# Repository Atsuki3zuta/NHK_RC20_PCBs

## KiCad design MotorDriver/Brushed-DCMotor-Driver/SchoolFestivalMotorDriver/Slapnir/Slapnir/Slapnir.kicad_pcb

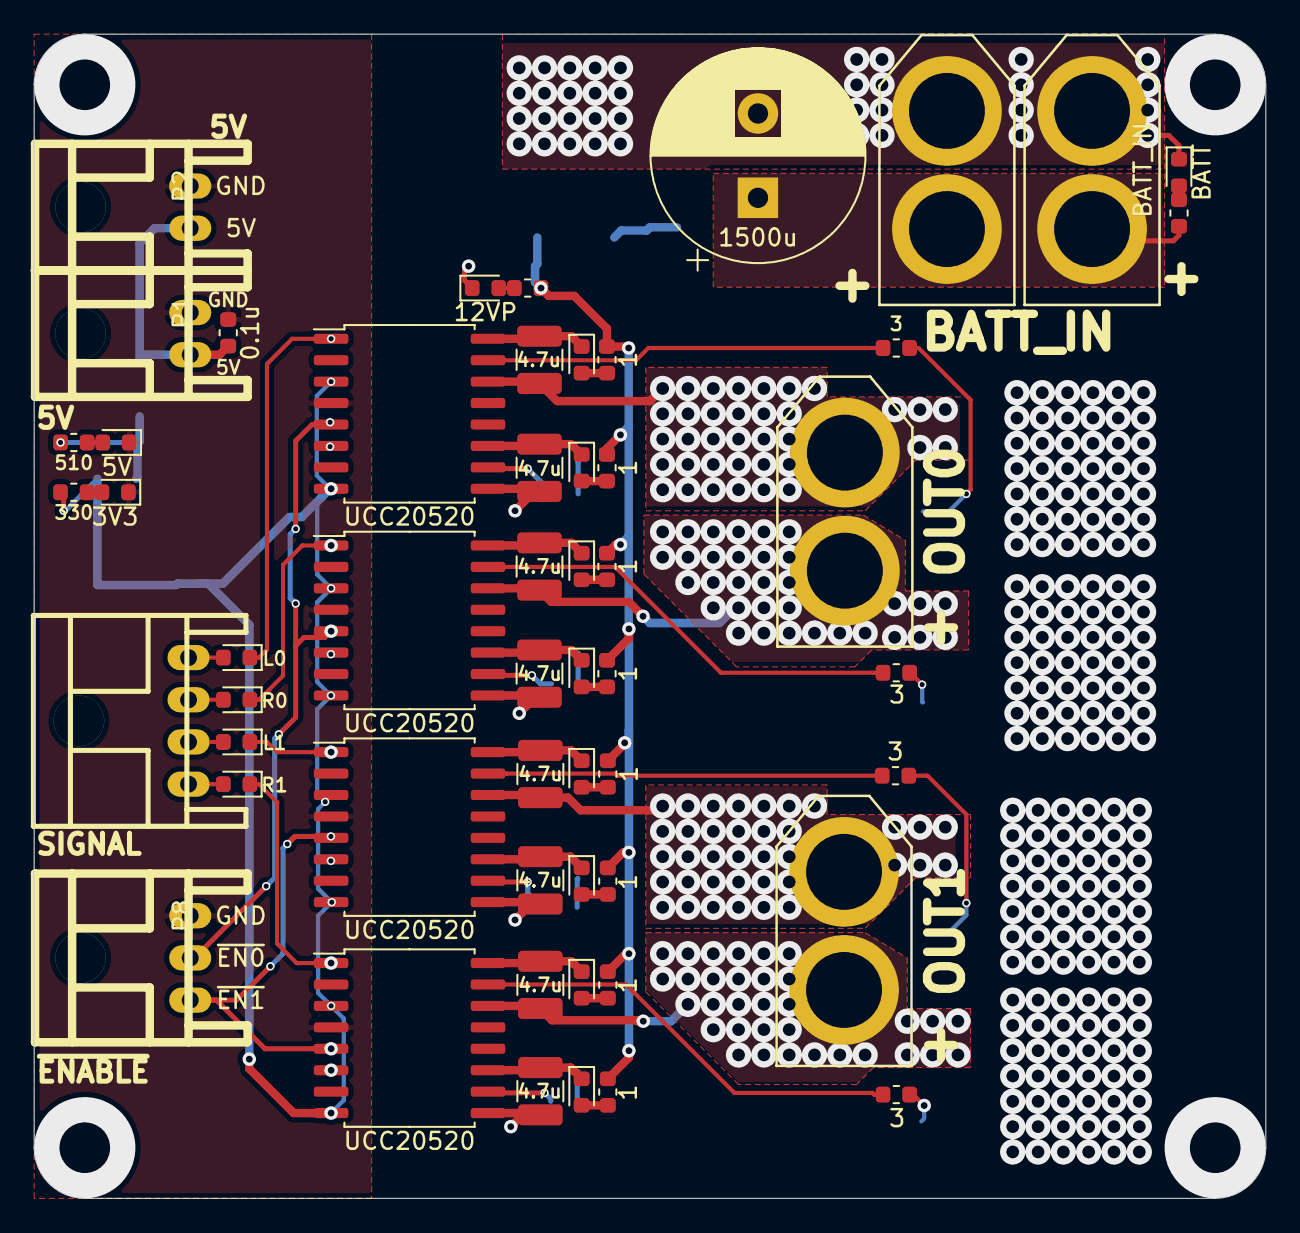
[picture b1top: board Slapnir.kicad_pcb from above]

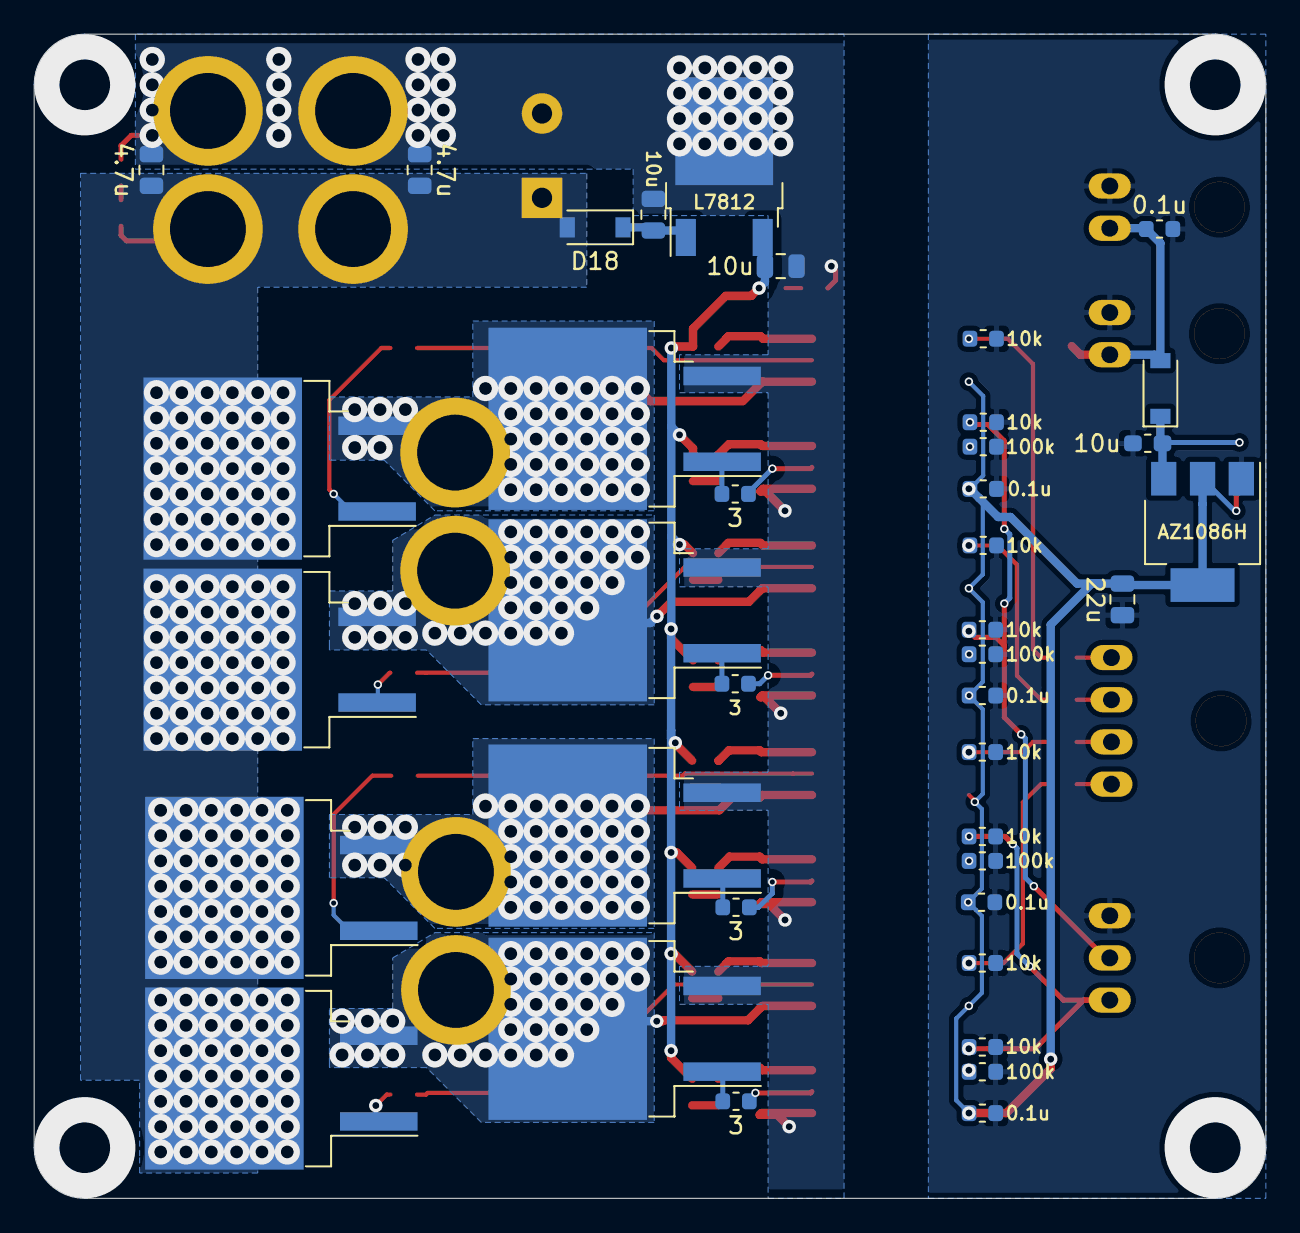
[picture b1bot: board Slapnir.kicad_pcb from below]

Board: 2 copper layers, 73.0 x 69.0 mm, 93 parts (39 on the bottom side), 62 nets.

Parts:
C1: 10u; C_0603_1608Metric_Pad1.05x0.95mm_HandSolder
C2, C3, C5, C6, C7, C8: 0.1u; C_0603_1608Metric
C4: 22u; C_0805_2012Metric
C9, C10, C11, C12, C13, C14, C15, C16: 4.7u; C_1210_3225Metric
C17: 1500u; CP_Radial_D12.5mm_P5.00mm
C18, C20: 4.7u; C_0805_2012Metric
C19, C21: 10u; C_0805_2012Metric
D1, D18: DIODE; D_SOD-123
D2, D3, D4, D5, D8, D9, D10, D11, D12, D13, D14, D15: DIODESCH; D_0603_1608Metric
D6: 5V; LED_0603_1608Metric
D7: 3V3; LED_0603_1608Metric
D16: BATT; LED_0603_1608Metric
D17: 12VP; LED_0603_1608Metric
P1, P2: 5V; XA_2LC
P3: SIGNAL; XA_4LC
P4: BATT_IN; XT60_F
P5: BATT_IN; XT60_M
P6: OUT0; XT60_F
P7: OUT1; XT60_F
P8: ~ENABLE; XA_3LC
Q1, Q2, Q3, Q4, Q5, Q6, Q7, Q8: Q_NMOS_GDS; TO-263-2
R1: 510; R_0603_1608Metric
R2: 330; R_0603_1608Metric
R3, R4, R5, R6, R29, R30, R31, R32: 10k; R_0603_1608Metric
R7, R8, R9, R10: 100k; R_0603_1608Metric
R11, R12, R13, R14, R15, R16, R17, R18: 3; R_0603_1608Metric
R19, R20, R21, R22, R23, R24, R25, R26: 1; R_0603_1608Metric
R27: 2.2k; R_0603_1608Metric
R28: 1.2k; R_0603_1608Metric
U1: AZ1086H; SOT-223-3_TabPin2
U2, U3, U4, U5: UCC20520; SOIC-16W_7.5x10.3mm_P1.27mm
U6: L7812; TO-252-2

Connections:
+3V3: C4.1, C5.1, C6.1, C7.1, C8.1, R2.2, U1.2, U2.3, U2.8, U3.3, U3.8, U4.3, U4.8, U5.3, U5.8
+5V: C1.1, D1.1, R1.2, U1.3
+12P: C21.1, R19.1, R20.1, R21.1, R22.1, R23.1, R24.1, R25.1, R26.1, R28.2, U6.3
+BATT: C17.1, C18.2, C20.2, D18.2, P4.2, P5.2, Q1.2, Q3.2, Q5.2, Q7.2, R27.2
/5V: C2.2, C3.2, D1.2, P1.2, P2.2
/MOTOR0_OUT_L: C9.2, P6.1, Q1.3, Q2.2, U2.14
/MOTOR0_OUT_R: C11.2, P6.2, Q3.3, Q4.2, U3.14
/MOTOR1_OUT_L: C13.2, P7.1, Q5.3, Q6.2, U4.14
/MOTOR1_OUT_R: C15.2, P7.2, Q7.3, Q8.2, U5.14
/PWM0_L: D2.1, R29.1, U2.1
/PWM0_R: D3.1, R30.1, U3.1
/PWM1_L: D4.1, R31.1, U4.1
/PWM1_R: D5.1, R32.1, U5.1
/~EN0: P8.2, R3.1, R4.1, U2.5, U3.5
/~EN1: P8.3, R5.1, R6.1, U4.5, U5.5
GND: C1.2, C2.1, C3.1, C4.2, C5.2, C6.2, C7.2, C8.2, D6.1, D7.1, P1.1, P2.1, P8.1, R3.2, R4.2, R5.2, R6.2, R7.2, R8.2, R9.2, R10.2, R29.2, R30.2, R31.2, R32.2, U1.1, U2.4, U3.4, U4.4, U5.4
GNDPWR: C10.2, C12.2, C14.2, C16.2, C17.2, C18.1, C19.2, C20.1, C21.2, D16.1, D17.1, P4.1, P5.1, Q2.3, Q4.3, Q6.3, Q8.3, U2.9, U3.9, U4.9, U5.9, U6.2
unnamed: C9.1, D8.1, U2.16
unnamed: C10.1, D9.1, U2.11
unnamed: C11.1, D10.1, U3.16
unnamed: C12.1, D11.1, U3.11
unnamed: C13.1, D12.1, U4.16
unnamed: C14.1, D13.1, U4.11
unnamed: C15.1, D14.1, U5.16
unnamed: C16.1, D15.1, U5.11
unnamed: C19.1, D18.1, U6.1
unnamed: D2.2, P3.1
unnamed: D3.2, P3.2
unnamed: D4.2, P3.3
unnamed: D5.2, P3.4
unnamed: D6.2, R1.1
unnamed: D7.2, R2.1
unnamed: D8.2, R19.2
unnamed: D9.2, R20.2
unnamed: D10.2, R21.2
unnamed: D11.2, R22.2
unnamed: D12.2, R23.2
unnamed: D13.2, R24.2
unnamed: D14.2, R25.2
unnamed: D15.2, R26.2
unnamed: D16.2, R27.1
unnamed: D17.2, R28.1
unnamed: Q1.1, R11.1
unnamed: Q2.1, R12.1
unnamed: Q3.1, R13.1
unnamed: Q4.1, R14.1
unnamed: Q5.1, R15.1
unnamed: Q6.1, R16.1
unnamed: Q7.1, R17.1
unnamed: Q8.1, R18.1
unnamed: R7.1, U2.6
unnamed: R8.1, U3.6
unnamed: R9.1, U4.6
unnamed: R10.1, U5.6
unnamed: R11.2, U2.15
unnamed: R12.2, U2.10
unnamed: R13.2, U3.15
unnamed: R14.2, U3.10
unnamed: R15.2, U4.15
unnamed: R16.2, U4.10
unnamed: R17.2, U5.15
unnamed: R18.2, U5.10

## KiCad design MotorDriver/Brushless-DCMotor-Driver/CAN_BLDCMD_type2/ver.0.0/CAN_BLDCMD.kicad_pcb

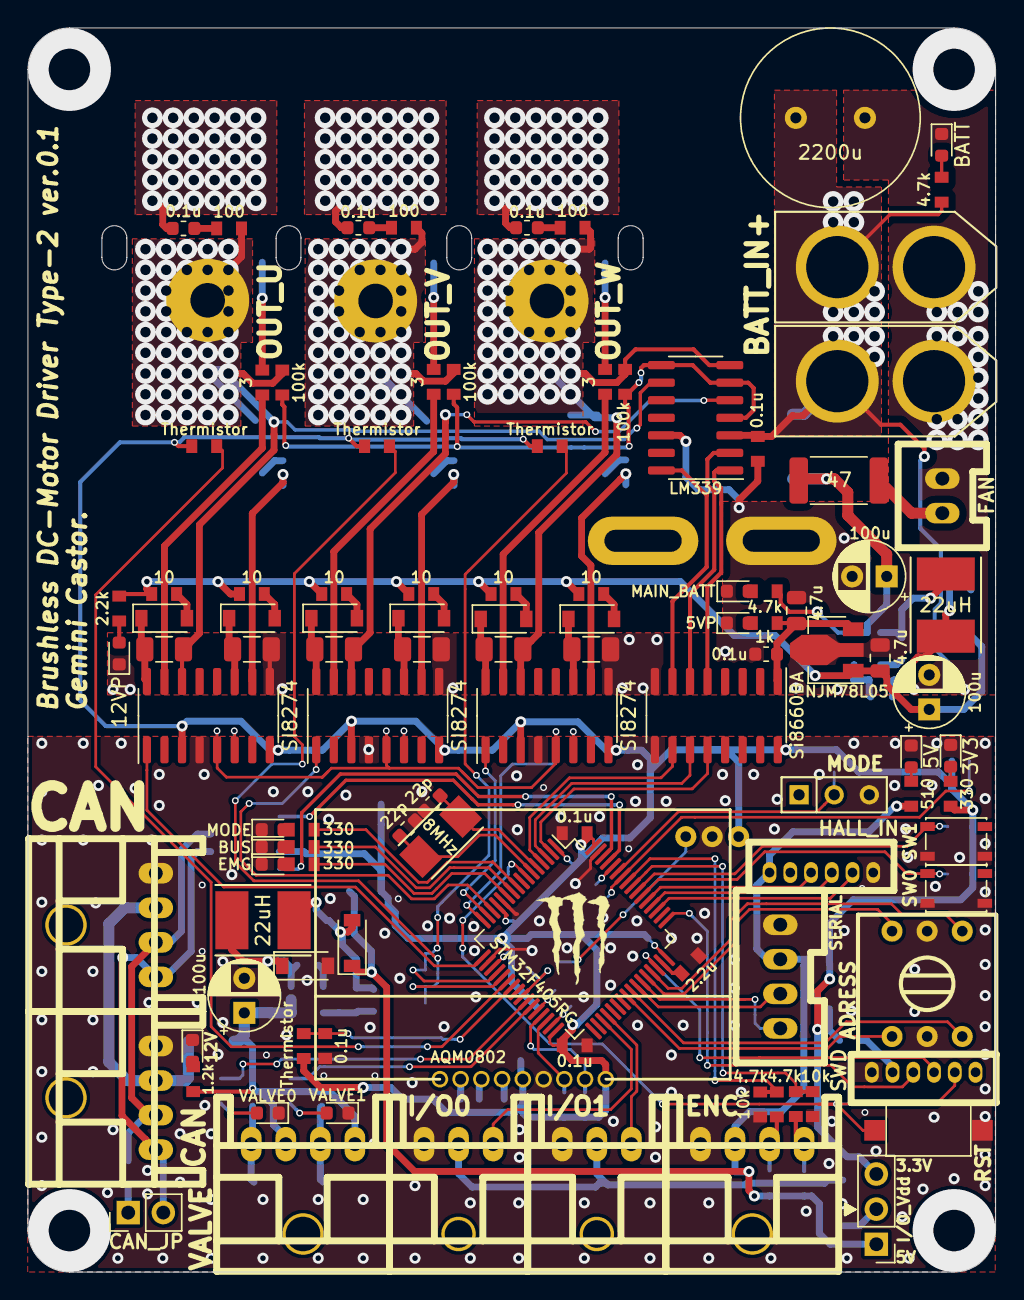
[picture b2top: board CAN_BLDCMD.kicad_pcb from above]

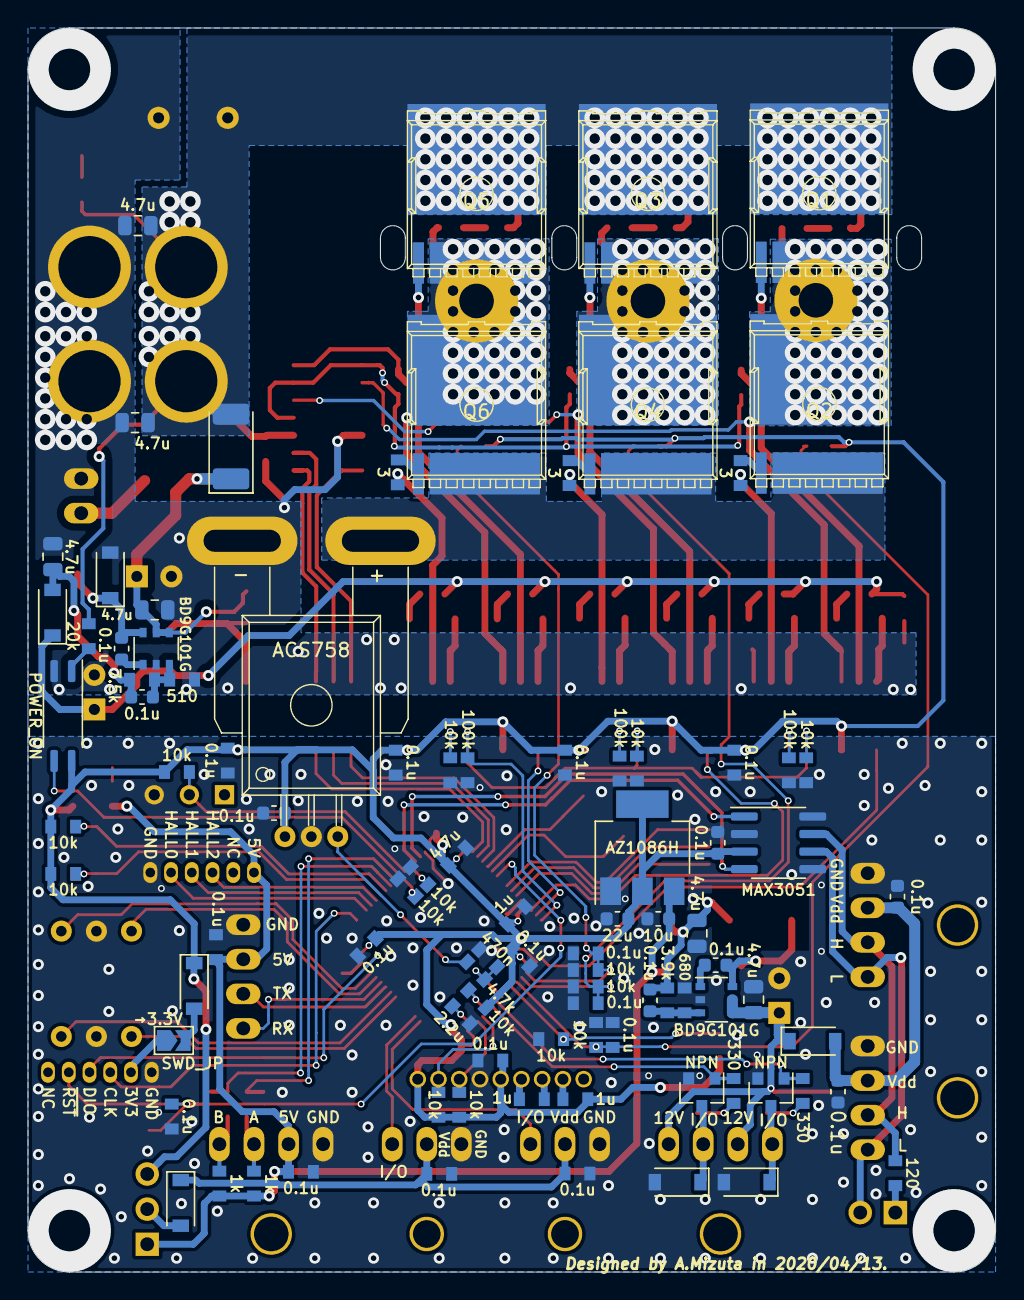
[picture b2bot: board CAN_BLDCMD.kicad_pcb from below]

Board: 2 copper layers, 70.0 x 90.0 mm, 203 parts (92 on the bottom side), 132 nets.

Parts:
C1, C2: 22p; C_0603_1608Metric
C3, C4, C8, C9, C10, C31, C32, C33, C34, C42, C43, C47: 0.1u; C_0603_1608Metric
C5, C6, C7, C11, C20, C22, C23, C24, C25, C26, C27, C28, C29, C35, C44, C45, C46, C63, C64: 0.1u; 1608_WP
C12, C18, C48, C55, C56, C57, C59, C60: 4.7u; C_0805_2012Metric
C13, C61, C62: 1u; 1608_WP
C14, C50, C58: 100u; CP_Radial_D5.0mm_P2.50mm
C15, C17: 2.2u; 1608_WP
C16: 4.7u; 1608_WP
C19: 10u; C_0603_1608Metric
C21: 22u; C_0603_1608Metric
C30: 470n; 1608_WP
C36, C37, C38, C39, C40, C41: 4.7u; C_1206_3216Metric
C49: 2200u; C_Radial_D13mm_H25.0mm_P5.00mm
D1, D2, D3, D4, D7, D8, D9, D10, D11, D12, D13, D14, D16, D17, D18: DIODE; D_SOD-123
D5: MODE; LED_0603_1608Metric
D6: BUS; LED_0603_1608Metric
D15: DIODE; D_2010_5025Metric_Pad1.52x2.65mm_HandSolder
D19: VALVE0; LED_0603_1608Metric
D20: VALVE1; LED_0603_1608Metric
D21: 12V; LED_0603_1608Metric
D22: 5V; LED_0603_1608Metric
D23: 3V3; LED_0603_1608Metric
D24: BATT; LED_0603_1608Metric
D25: MAIN_BATT; LED_0603_1608Metric
D26: 12VP; LED_0603_1608Metric
D27: 5VP; LED_0603_1608Metric
D28: EMG; LED_0603_1608Metric
ISO1: Si8660BA; SOIC-16_3.9x9.9mm_P1.27mm
J1: SWD; ZH_6P
J2, J3: CAN; XA_4L
J4: ENC; XA_4L
J5: I/O0; XA_3L
J6: I/O1; XA_3L
J7: SERIAL; XA_4P
J8: FAN; XA_2P
J9: BATT_IN; XT60_F
J10: BATT_IN; XT60_M
J11: OUT_U; SolderWirePad_1x01_Drill2.5mm
J12: OUT_V; SolderWirePad_1x01_Drill2.5mm
J13: OUT_W; SolderWirePad_1x01_Drill2.5mm
J14: VALVE; XA_4L
J15: HALL_IN; ZH_6P
JP1: SWD_JP; SolderJumper-2_P1.3mm_Open_TrianglePad1.0x1.5mm
JP2: CAN_JP; PinHeader_1x02_P2.54mm_Vertical
JP3: I/O_Vdd; PinHeader_1x03_P2.54mm_Vertical
L1, L2: 22uH; Inductor_Taiyo-Yuden_NR-50xx_HandSoldering
Q1, Q2, Q3, Q4, Q5, Q6: MOSFET_N; HSOF-8-1
Q7, Q8: NPN; SOT-23
R1, R5, R6, R7, R11, R15, R16, R17, R18, R19, R20, R21, R25, R26, R54, R55, R65: 10k; 1608_WP
R2: 3.9k; 1608_WP
R3: 680; 1608_WP
R4: 120; 1608_WP
R8, R9, R29, R61, R62: 4.7k; 1608_WP
R10, R12, R64: 1k; 1608_WP
R13, R14, R27, R56, R57, R60: 330; 1608_WP
R22, R23, R24, R28, R30, R31: 100k; 1608_WP
R32: 20k; 1608_WP
R33, R34, R35, R36, R37, R38: 3; 1608_WP
R39, R40, R41, R42, R43, R44: 10; 1608_WP
R45: 7.5k; 1608_WP
R46, R59: 510; 1608_WP
R47: 47; R_2512_6332Metric
R48, R49, R50: 100; 1608_WP
R58: 1.2k; 1608_WP
R63: 2.2k; 1608_WP
SW1: SW0; SW_SPST_PTS810
SW2: SW1; SW_SPST_PTS810
SW3: RST; SW_SPST_CK_RS282G05A3
SW4: MODE; SW_Micro_SPST
TH1, TH2, TH3, TH4: Thermistor; 1608_WP
U1: MAX3051; SOIC-8_3.9x4.9mm_P1.27mm
U2, U15: BD9G101G; TSOP-6_1.65x3.05mm_P0.95mm
U3: STM32F405RG; LQFP-64_10x10mm_P0.5mm
U4: AZ1086H; SOT-223-3_TabPin2
U5: ADRESS; rotary_0F
U6: POWER_ON; SOIC-4_4.55x2.6mm_P1.27mm
U7, U8, U9: SI8274; SOIC-16_3.9x9.9mm_P1.27mm
U10: LM339; SOIC-14_3.9x8.7mm_P1.27mm
U11: NJM78L05; SOT-89-3
U12: ACS758; ACS785xCB
U19: LOGO; Mini_Monster
U20: AQM0802; AQM0802_original
Y1: 8MHz; Crystal_SMD_5032_2Pads

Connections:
+3V3: C3.1, C5.1, C6.1, C7.1, C11.1, C13.1, C16.1, C21.1, C29.1, C33.1, C44.1, C45.1, C46.1, C61.2, C63.2, D1.1, ISO1.16, JP3.3, R7.1, R11.1, R15.1, R54.1, R55.1, R60.2, R65.1, TH1.1, TH2.1, TH3.1, TH4.1, U1.3, U3.1, U3.13, U3.19, U3.32, U3.48, U3.64, U4.2, U6.4, U7.3, U7.8, U8.3, U8.8, U9.3, U9.8, U12.1, U20.5, U20.9
+5V: C19.1, C20.2, C24.2, D4.1, J4.2, J7.2, J15.6, JP3.1, R10.2, R12.2, R59.2, U4.3
+5VP: C42.1, C60.1, ISO1.1, R64.2, U11.3
+12P: C58.1, C59.1, D16.1, R39.1, R40.1, R41.1, R42.1, R43.1, R44.1, R63.2, U11.1
+12V: C12.1, C14.1, D3.1, J14.2, J14.4, R58.2, U2.4, U2.5
+BATT: C31.2, C32.2, C34.2, C35.1, C49.1, C55.1, C57.1, D15.2, J9.2, J10.2, Q1.D, Q3.D, Q5.D, R32.1, R61.2, U10.3
+Batt: C48.1, C50.1, D15.1, R47.2, R62.2, U15.4, U15.5
/ADRESS_0: U3.41, U5.3
/ADRESS_1: U3.40, U5.1
/ADRESS_2: U3.45, U5.4
/ADRESS_3: U3.44, U5.6
/CAN1_RX: U1.4, U3.62
/CAN1_TX: U1.1, U3.61
/CAN_H: J2.3, J3.3, R4.2, U1.7
/CAN_L: J2.4, J3.4, JP2.2, U1.6
/Current: C30.2, R29.2, U3.25
/Drive_U_Temp: C25.1, R16.1, TH1.2, U3.22
/Drive_V_Temp: C26.1, R17.1, TH2.2, U3.21
/Drive_W_Temp: C27.1, R18.1, TH3.2, U3.20
/Enable: R20.1, R21.1, R22.1, U3.16, U7.5, U8.5, U9.5
/FB_5V: C4.1, C18.1, D4.2, L1.2, R2.1
/FB_12P: C43.2, C56.1, D16.2, L2.2, R45.1
/HALL_0: J15.2, U3.51
/HALL_1: J15.3, U3.52
/HALL_2: J15.4, U3.53
/I2Cx_SCL: R54.2, U3.29, U20.8
/I2Cx_SDA: R55.2, U3.30, U20.7
/INVERTER_OUT: Q2.S, Q4.S, Q6.S, U12.4
/IO0_Pin: J5.3, U3.35
/IO1_Pin: J6.3, U3.36
/LED0: R13.1, U3.9
/LED1: R14.1, U3.10
/LED2: R27.1, U3.11
/LOCATION_U_SIGNAL: ISO1.10, U3.4
/LOCATION_V_SIGNAL: ISO1.11, U3.3
/LOCATION_W_SIGNAL: ISO1.12, U3.2
/OSC_IN: C1.1, U3.5, Y1.1
/OSC_OUT: C2.1, U3.6, Y1.2
/OUT_U: C36.2, J11.1, Q1.S, Q2.D, R28.1, R48.2, U7.14, U10.9
/OUT_V: C38.2, J12.1, Q3.S, Q4.D, R30.1, R49.2, U8.14, U10.5
/OUT_W: C40.2, J13.1, Q5.S, Q6.D, R31.1, R50.2, U9.14, U10.7
/PWM_U: U3.17, U7.1
/PWM_V: U3.14, U8.1
/PWM_W: U3.15, U9.1
/PWR_ON_Pin: R26.1, U3.58, U6.3
/SIGNAL_U: ISO1.7, U10.14
/SIGNAL_V: ISO1.6, U10.2
/SIGNAL_W: ISO1.5, U10.1
/SW0: R7.2, SW1.2, U3.54
/SW1: R11.2, SW2.2, U3.55
/SWCLK: J1.3, U3.49
/SWDIO: J1.4, U3.46
/SW_MODE: R65.2, SW4.2, U3.59
/Subscribe_Temp: C28.1, R19.1, TH4.2, U3.23
/TIMx_CH1: R5.2, R9.2, U3.56
/TIMx_CH2: R6.2, R8.2, U3.57
/USARTX_RX: J7.4, U3.43
/USARTX_TX: J7.3, U3.42
/VALVE_0: Q7.1, R56.1, U3.26
/VALVE_1: Q8.1, R57.1, U3.27
/ZERO_CROSS: R28.2, R30.2, R31.2, U10.4, U10.6, U10.8
/~RST: C64.2, J1.5, SW3.2, U3.7
CAN_Vdd: C9.1, C10.1, D3.2, J2.2, J3.2
GND: C1.2, C2.2, C3.2, C5.2, C6.2, C7.2, C9.2, C10.2, C11.2, C12.2, C13.2, C14.2, C15.2, C16.2, C17.2, C18.2, C19.2, C20.1, C21.2, C22.1, C23.1, C24.1, C25.2, C26.2, C27.2, C28.2, C29.2, C30.1, C33.2, C44.2, C45.2, C46.2, C63.1, C64.1, D2.2, D5.1, D6.1, D17.2, D18.2, D19.1, D20.1, D21.1, D22.1, D23.1, D28.1, ISO1.9, J1.1, J2.1, J3.1, J4.1, J5.1, J6.1, J7.1, J15.1, Q7.2, Q8.2, R1.2, R3.2, R5.1, R6.1, R16.2, R17.2, R18.2, R19.2, R20.2, R21.2, R22.2, R23.2, R24.2, R25.2, R26.2, SW1.1, SW2.1, SW3.1, SW4.3, U1.2, U1.5, U1.8, U2.2, U3.12, U3.18, U3.63, U4.1, U5.2, U5.5, U7.4, U8.4, U9.4, U12.2, U20.6
GNDPWR: C35.2, C37.2, C39.2, C41.2, C42.2, C48.2, C49.2, C50.2, C55.2, C56.2, C57.2, C58.2, C59.2, C60.2, D14.2, D24.1, D25.1, D26.1, D27.1, ISO1.8, J8.1, J9.1, J10.1, R46.2, U6.2, U7.9, U8.9, U9.9, U10.12, U11.2, U12.5, U15.2
IO_Vdd: C22.2, C23.2, D7.1, J5.2, J6.2
unnamed: C4.2, R2.2, R3.1, U2.3
unnamed: C8.1, D2.1, L1.1, U2.6
unnamed: C8.2, U2.1
unnamed: C15.1, U3.31
unnamed: C17.1, U3.47
unnamed: C31.1, R48.1
unnamed: C32.1, R49.1
unnamed: C34.1, R50.1
unnamed: C36.1, D8.1, U7.16
unnamed: C37.1, D9.1, U7.11
unnamed: C38.1, D10.1, U8.16
unnamed: C39.1, D11.1, U8.11
unnamed: C40.1, D12.1, U9.16
unnamed: C41.1, D13.1, U9.11
unnamed: C43.1, R45.2, R46.1, U15.3
unnamed: C47.1, D14.1, L2.1, U15.6
unnamed: C47.2, U15.1
unnamed: C61.1, U20.2
unnamed: C62.1, U20.3
unnamed: C62.2, U20.4
unnamed: D1.2, JP1.2
unnamed: D5.2, R13.2
unnamed: D6.2, R14.2
unnamed: D7.2, JP3.2
unnamed: D8.2, R39.2
unnamed: D9.2, R40.2
unnamed: D10.2, R41.2
unnamed: D11.2, R42.2
unnamed: D12.2, R43.2
unnamed: D13.2, R44.2
unnamed: D17.1, J14.1, Q7.3
unnamed: D18.1, J14.3, Q8.3
unnamed: D19.2, R56.2
unnamed: D20.2, R57.2
unnamed: D21.2, R58.1
unnamed: D22.2, R59.1
unnamed: D23.2, R60.1
unnamed: D24.2, R61.1
unnamed: D25.2, R62.1
unnamed: D26.2, R63.1
unnamed: D27.2, R64.1
unnamed: D28.2, R27.2
unnamed: J1.2, JP1.1
unnamed: J4.3, R8.1, R12.1
unnamed: J4.4, R9.1, R10.1
unnamed: J8.2, R47.1
unnamed: JP2.1, R4.1
unnamed: Q1.G, R33.1
unnamed: Q2.G, R34.1
unnamed: Q3.G, R35.1
unnamed: Q4.G, R36.1
unnamed: Q5.G, R37.1
unnamed: Q6.G, R38.1
unnamed: R1.1, U3.60
unnamed: R15.2, U3.28
unnamed: R23.1, U7.6
unnamed: R24.1, U8.6
unnamed: R25.1, U9.6
unnamed: R29.1, U12.3
unnamed: R32.2, U6.1
unnamed: R33.2, U7.15
unnamed: R34.2, U7.10
unnamed: R35.2, U8.15
unnamed: R36.2, U8.10
unnamed: R37.2, U9.15
unnamed: R38.2, U9.10

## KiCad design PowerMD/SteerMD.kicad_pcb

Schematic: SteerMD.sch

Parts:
C1, C3: 22p; C_0603_1608Metric
C2, C5, C6, C7, C8, C9, C11, C15, C16, C18, C21, C22, C23, C24, C26, C36, C38, C39, C42, C44, C53, C54, C55, C58, C59, C60, C61: 0.1u; C_0603_1608Metric
C4, C17, C40, C41, C52: 0.1u; 1608_WP
C10, C63: 1u; C_0603_1608Metric
C12: 4.7u; 1608_WP
C13, C14: 2.2u; C_0603_1608Metric
C19, C20, C30, C31, C45, C46, C48, C49: 4.7u; C_1206_3216Metric
C25, C33, C64: 100u; CP_Radial_D5.0mm_P2.50mm
C28: 10u; C_0805_2012Metric
C29, C32, C35, C37, C43: 4.7u; C_0805_2012Metric
C34: 2200u; C_Radial_D13.0mm_H25.0mm_P5.00mm
C47, C50: 470n; C_0603_1608Metric
C56: 10u; C_0603_1608Metric
C57: 22u; C_0603_1608Metric
C62: 1u; 1608_WP
D1, D2, D3, D11, D13, D14, D19, D20: DIODE; 1608_WP
D4, D5, D16, D18, D24, D26: DIODE; D_SOD-123
D7: EMG1; LED_0603_1608Metric
D8: BUS1; LED_0603_1608Metric
D9: EMG0; LED_0603_1608Metric
D15: DIODE; D_SMA
D21: BATT; LED_0603_1608Metric
D22: 12VP; LED_0603_1608Metric
D23: 3V3P; LED_0603_1608Metric
D27: Main_BATT; LED_0603_1608Metric
D32: 12V; LED_0603_1608Metric
D33: 5V; LED_0603_1608Metric
D34: 3.3V; LED_0603_1608Metric
D39: BUS0; LED_0603_1608Metric
JP1: SWD_3V3; SolderJumper-2_P1.3mm_Open_TrianglePad1.0x1.5mm
JP2: CAN_JP; PinHeader_1x02_P2.54mm_Vertical
JP3: I/O_Vdd; SW_Micro_SPST
L1, L2: 22uH; Inductor_Taiyo-Yuden_NR-60xx_HandSoldering
P1: SWD; ZH_6P
P2: MOTOR_COOLING; XA_4L
P3, P4: CAN; XA_4L
P5: SERIAL; XA_4P
P6: I/O_0; XA_3LC
P7: FAN; XA_2P
P8: BATT_IN; XT60_M
P9: BATT_IN; XT60_F
P10: OUT_1; XT60_F
P11: ENC_0; XA_4L
P13: ENC_1; XA_4L
P14: I/O_1; XA_3LC
P15: OUT_0; XT60_F
Q1, Q2, Q3, Q4, Q5, Q6, Q7, Q8: MOSFET_N; HSOF-8-1
R1, R4, R5, R9, R22, R38: 10k; R_0603_1608Metric
R2, R10, R26, R27, R36, R39, R52, R61, R62, R66, R67, R68, R69, R70, R73, R74: 10k; 1608_WP
R3: 120; R_0603_1608Metric
R6, R7, R8, R49, R51: 330; R_0603_1608Metric
R11, R13, R35, R65: 100k; 1608_WP
R12: 330; 1608_WP
R14: 7.5k; R_0603_1608Metric
R15, R34, R48: 510; R_0603_1608Metric
R16, R32, R40, R41, R57, R60: 4.7k; R_0603_1608Metric
R17, R18, R30, R31, R53, R54, R63, R64: FILTER; R_0603_1608Metric
R19, R20, R28, R29, R55, R56, R58, R59: 1; 1608_WP
R21, R24, R42, R43: 1k; 1608_WP
R23: 1k; R_0603_1608Metric
R25: 47; R_2812
R33: 2.2k; R_0603_1608Metric
R37: 50k; R_0603_1608Metric
R44, R45, R46, R50: 4.7k; 1608_WP
R47: 1.2k; R_0603_1608Metric
R71, R72: 12; R_2812
SW1: RST; SW_SPST_CK_RS282G05A3
SW3: SW0; SW_SPST_CK_RS282G05A3
SW4: SW1; SW_SPST_CK_RS282G05A3
TH1, TH2, TH3, TH4, TH5: Thermistor; C_0603_1608Metric
U1: MAX3051; SOIC-8_3.9x4.9mm_P1.27mm
U2: BD9G101; TSOP-6_1.65x3.05mm_P0.95mm
U3: STM32F405RG; LQFP-64_10x10mm_P0.5mm
U4, U8, U12, U14: SI8274; SOIC-16_3.9x9.9mm_P1.27mm
U5: SI8900; SOIC-16W_7.5x10.3mm_P1.27mm
U6: ADC_~RST; SO-4_4.4x2.3mm_P1.27mm
U7: BD9G101G; TSOP-6_1.65x3.05mm_P0.95mm
U9: BD33FA1; SOT-89-3
U10, U13: ACS758; ACS785xCB
U11: POWER_ON; SO-4_4.4x2.3mm_P1.27mm
U15: AZ1086H; SOT-223-3_TabPin2
U16: LOGO; Mini_Monster
U17: AQM0802; AQM0802_original
U19: ADRESS; rotary_0F
Y1: 8MHz; Crystal_SMD_5032_2Pads

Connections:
+3.3VP: C22.1, C32.1, R16.1, R34.2, U5.1 (VDDA), U5.2 (VREF), U9.1 (Vo)
+3V3: C4.1, C5.1, C6.1, C8.1, C9.1, C10.1, C12.1, C17.1, C21.1, C36.1, C40.1, C41.1, C42.1, C52.1, C57.1, C61.2, C62.2, D4.1 (K), JP3.1, R9.1, R49.2, R73.1, R74.1, TH1.1, TH2.1, TH3.1, TH4.1, TH5.1, U1.3 (VDD), U3.1 (VBAT), U3.13 (VDDA), U3.19 (VDD), U3.32 (VDD), U3.48 (VDD), U3.64 (VDD), U4.3 (VDDI), U4.8 (VDDI), U5.10 (VDDB), U5.16 (VDDB), U8.3 (VDDI), U8.8 (VDDI), U10.1 (VCC), U11.4, U12.3 (VDDI), U12.8 (VDDI), U13.1 (VCC), U14.3 (VDDI), U14.8 (VDDI), U15.2 (V_OUT), U17.5 (VDD), U17.9 (/RST)
+5V: C15.2, C26.2, C44.2, C56.1, D26.1 (K), JP3.3, P5.2, P11.2, P13.2, R4.1, R5.1, R21.1, R24.1, R42.1, R43.1, R48.2, U15.3 (V_IN)
+12P: C29.1, C64.1, D18.1 (K), R19.1, R20.1, R28.1, R29.1, R33.2, R55.1, R56.1, R58.1, R59.1, U9.3 (Vcc)
+12V: C33.1, C38.1, D5.1 (K), R47.2, R71.2, R72.2, U2.4 (EN), U2.5 (IN)
+BATT: C34.1, C35.1, C43.1, D15.2 (A), P8.2, P9.2, R22.1, R32.2, U10.4 (IP+), U11.1, U13.4 (IP+)
/ADC_~RST: R16.2, U5.7 (~RST~), U6.4
/ADC_~RST~_PIN: U3.45 (CAN1_TX/PA12), U6.1
/ADR_1: U3.23 (ADC12_IN7/TIM1_CH1N/TIM8_CH1N/TIM14_CH1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), U19.3 (1)
/ADR_2: U3.27 (ADC12_IN9/TIM1_CH3N/TIM8_CH3N/TIM3_CH4/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), U19.1 (2)
/ADR_4: U3.21 (ADC12_IN5/TIM2_CH1_ETR/TIM8_CH1N/PA5), U19.4
/ADR_8: U3.22 (ADC12_IN6/TIM3_CH1/TIM13_CH1/PA6), U19.6 (8)
/CAN1_RX: U1.4 (RXD), U3.61 (TIM4_CH3/TIM10_CH1/CAN1_RX/PB8)
/CAN1_TX: U1.1 (TXD), U3.62 (TIM4_CH4/TIM11_CH1/CAN1_TX/PB9)
/CAN_H: JP2.1, P3.3, P4.3, U1.7 (CANH)
/CAN_L: P3.4, P4.4, R3.1, U1.6 (CANL)
/CAN_Vdd: C7.2, C11.2, D5.2 (A), P3.2, P4.2
/CounterVoltage0: U5.4 (AIN1)
/CounterVoltage1: U5.5 (AIN2)
/Current0: C50.1, R60.2, U3.11 (PC3/ADC12_IN13)
/Current1: C47.1, R57.2, U3.10 (PC2/ADC12_IN12)
/EN0: R10.1, R36.1, U3.37 (PC6/TIM8_CH1/USART6_TX/TIM3_CH1), U4.5 (DISABLE), U12.5 (DISABLE)
/EN1: R2.1, R66.1, U3.34 (TIM1_CH1N/CAN2_TX/PB13), U8.5 (DISABLE), U14.5 (DISABLE)
/FB: R37.2, R38.1, U2.3 (FB)
/FB_PWR: C18.2, R14.2, R15.1, U7.3 (FB)
/FB_PWR_OUT: C18.1, C28.1, D18.2 (A), L1.2, R14.1
/I2C2_SCL: R73.2, U3.29 (USART3_TX/TIM2_CH3/PB10), U17.8 (SCL)
/I2C2_SDA: R74.2, U3.30 (USART3_RX/TIM2_CH4/PB11), U17.7 (SDA)
/IO_0: P6.3, U3.2 (PC13)
/IO_1: P14.3, U3.3 (PC14/OSC32_IN)
/LED0: R6.1, U3.52 (PC11/UART4_RX/USART3_RX)
/LED1: R7.1, U3.53 (PC12/UART5_TX)
/LED2: R8.1, U3.54 (PD2/UART5_RX)
/LED3: R51.1, U3.55 (TIM2_CH2/PB3)
/MOTOR0_BATT: Q1.D, Q5.D, U10.5 (IP-)
/MOTOR1_BATT: Q3.D, Q7.D, U13.5 (IP-)
/Motor0L_Tmp: C53.1, R67.1, TH1.2, U3.9 (PC1/ADC12_IN11)
/Motor0R_Tmp: C58.1, R52.1, TH3.2, U3.8 (PC0/ADC12_IN10)
/Motor1L_Tmp: C54.1, R68.1, TH2.2, U3.26 (ADC12_IN8/TIM1_CH2N/TIM8_CH2N/TIM3_CH3/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)
/Motor1R_Tmp: C59.1, R69.1, TH4.2, U3.25 (PC5/ADC12_IN15)
/OSC_IN: C1.2, U3.5 (OSC_IN), Y1.1
/OSC_OUT: C3.2, U3.6 (OSC_OUT), Y1.2
/OUT0_L: C19.2, P15.1, Q1.S, Q2.D, U4.14 (GNDA)
/OUT0_R: C30.2, P15.2, Q5.S, Q6.D, U12.14 (GNDA)
/OUT1_L: C45.2, P10.1, Q3.S, Q4.D, U8.14 (GNDA)
/OUT1_R: C48.2, P10.2, Q7.S, Q8.D, U14.14 (GNDA)
/PWM0_L: U3.38 (PC7/TIM8_CH2/USART6_RX/TIM3_CH2), U4.1 (PWM)
/PWM0_R: U3.39 (PC8/TIM8_CH3/TIM3_CH3), U12.1 (PWM)
/PWM1_L: U3.36 (TIM1_CH3N/TIM8_CH3N/TIM12_CH2/PB15), U8.1 (PWM)
/PWM1_R: U3.35 (TIM1_CH2N/TIM8_CH2N/TIM12_CH1/PB14), U14.1 (PWM)
/PWR_ON_PIN: R39.1, U3.44 (CAN1_RX/TIM1_CH4/PA11), U11.3
/SW0: R4.2, SW3.2, U3.41 (TIM1_CH1/PA8)
/SW1: R5.2, SW4.2, U3.40 (PC9/TIM8_CH4/TIM3_CH4)
/SWCLK: P1.3, U3.49 (SWCLK/PA14)
/SWDIO: P1.4, U3.46 (SWDIO/PA13)
/Substrate_Temp: C60.1, R70.1, TH5.2, U3.20 (ADC12_IN4/PA4)
/TIM3_CH1: R26.1, R44.2, U3.56 (TIM3_CH1/PB4)
/TIM3_CH2: R45.2, R61.1, U3.57 (CAN2_RX/TIM3_CH2/PB5)
/TIM4_CH1: R27.1, R46.2, U3.58 (TIM4_CH1/CAN2_TX/USART1_TX/PB6)
/TIM4_CH2: R50.2, R62.1, U3.59 (USART1_RX/TIM4_CH2/PB7)
/USART1_RX: U3.43 (USART1_RX/TIM1_CH3/PA10), U5.12 (TX)
/USART1_TX: U3.42 (USART1_TX/TIM1_CH2/PA9), U5.13 (RX)
/USART2_RX: P5.4, U3.17 (USART2_RX/TIM5_CH4/TIM9_CH2/ADC12_IN3/T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)
/USART2_TX: P5.3, U3.16 (USART2_TX/TIM5_CH3/TIM9_CH1/ADC12_IN2/T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)
/Voltage: C24.1, R22.2, R23.1, U5.3 (AIN0)
/batt: C25.1, C37.1, D15.1 (K), R25.2, R41.2, U7.4 (EN), U7.5 (VCC)
/~RST: C2.2, P1.5, SW1.1, U3.7 (~RST)
GND: C1.1, C2.1, C3.1, C4.2, C5.2, C6.2, C7.1, C8.2, C9.2, C10.2, C11.1, C12.2, C13.2, C14.2, C15.1, C16.1, C17.2, C21.2, C26.1, C33.2, C36.2, C38.2, C40.2, C41.2, C42.2, C44.1, C47.2, C50.2, C52.2, C53.2, C54.2, C55.1, C56.2, C57.2, C58.2, C59.2, C60.2, C61.1, D7.1 (K), D8.1 (K), D9.1 (K), D24.2 (A), D32.1 (K), D33.1 (K), D34.1 (K), D39.1 (K), P1.1, P2.1, P2.3, P3.1, P4.1, P5.1, P6.1, P11.1, P13.1, P14.1, R1.2, R2.2, R10.2, R11.2, R12.2, R13.2, R26.2, R27.2, R35.2, R36.2, R38.2, R39.2, R52.2, R61.2, R62.2, R65.2, R66.2, R67.2, R68.2, R69.2, R70.2, SW1.2, SW3.1, SW4.1, U1.2 (GND), U1.5 (SHDN), U1.8 (RS), U2.2 (GND), U3.12 (VSSA), U3.18 (VSS), U3.63 (VSS), U4.4 (GNDI), U5.9 (GNDB), U8.4 (GNDI), U10.2 (GND), U12.4 (GNDI), U13.2 (GND), U14.4 (GNDI), U15.1 (GND), U17.6 (VSS), U19.2 (C), U19.5 (C)
GNDPWR: C20.2, C22.2, C24.2, C25.2, C28.2, C29.2, C31.2, C32.2, C34.2, C35.2, C37.2, C43.2, C46.2, C49.2, C64.2, D16.2 (A), D21.1 (K), D22.1 (K), D23.1 (K), D27.1 (K), P7.1, P8.1, P9.1, Q2.S, Q4.S, Q6.S, Q8.S, R15.2, R23.2, R40.2, U4.9 (GNCB), U5.8 (GNDA), U6.3, U7.2 (GND), U8.9 (GNCB), U9.2 (FIN), U12.9 (GNCB), U14.9 (GNCB)
IO_Vdd: C16.2, C55.2, JP3.2, P6.2, P14.2
unnamed: C13.1, U3.31 (VCAP_1)
unnamed: C14.1, U3.47 (VCAP_2)
unnamed: C19.1, D13.1 (K), U4.16 (VDDA)
unnamed: C20.1, D14.1 (K), U4.11 (VDDB)
unnamed: C23.1, D16.1 (K), L1.1, U7.6 (Lx)
unnamed: C23.2, U7.1 (BST)
unnamed: C30.1, D19.1 (K), U12.16 (VDDA)
unnamed: C31.1, D20.1 (K), U12.11 (VDDB)
unnamed: C39.1, D24.1 (K), L2.1, U2.6 (SW)
unnamed: C39.2, U2.1 (BS)
unnamed: C45.1, D1.1 (K), U8.16 (VDDA)
unnamed: C46.1, D2.1 (K), U8.11 (VDDB)
unnamed: C48.1, D3.1 (K), U14.16 (VDDA)
unnamed: C49.1, D11.1 (K), U14.11 (VDDB)
unnamed: C62.1, U17.2 (VOUT)
unnamed: C63.1, U17.3 (CAP1N)
unnamed: C63.2, U17.4 (CAP1P)
unnamed: D1.2 (A), R55.2
unnamed: D2.2 (A), R56.2
unnamed: D3.2 (A), R58.2
unnamed: D4.2 (A), JP1.2
unnamed: D7.2 (A), R6.2
unnamed: D8.2 (A), R7.2
unnamed: D9.2 (A), R8.2
unnamed: D11.2 (A), R59.2
unnamed: D13.2 (A), R19.2
unnamed: D14.2 (A), R20.2
unnamed: D19.2 (A), R28.2
unnamed: D20.2 (A), R29.2
unnamed: D21.2 (A), R32.1
unnamed: D22.2 (A), R33.1
unnamed: D23.2 (A), R34.1
unnamed: D26.2 (A), L2.2, R37.1
unnamed: D27.2 (A), R41.1
unnamed: D32.2 (A), R47.1
unnamed: D33.2 (A), R48.1
unnamed: D34.2 (A), R49.1
unnamed: D39.2 (A), R51.2
unnamed: JP1.1, P1.2
unnamed: JP2.2, R3.2
unnamed: P2.2, R71.1
unnamed: P2.4, R72.1
unnamed: P7.2, R25.1
unnamed: P11.3, R43.2, R45.1
unnamed: P11.4, R42.2, R44.1
unnamed: P13.3, R24.2, R50.1
unnamed: P13.4, R21.2, R46.1
unnamed: Q1.G, R17.1
unnamed: Q2.G, R18.1
unnamed: Q3.G, R53.1
unnamed: Q4.G, R54.1
unnamed: Q5.G, R30.1
unnamed: Q6.G, R31.1
unnamed: Q7.G, R63.1
unnamed: Q8.G, R64.1
unnamed: R1.1, U3.60 (BOOT0)
unnamed: R9.2, U3.28 (BOOT1/PB2)
unnamed: R11.1, U4.6 (DT)
unnamed: R12.1, U6.2
unnamed: R13.1, U8.6 (DT)
unnamed: R17.2, U4.15 (VOA)
unnamed: R18.2, U4.10 (VOB)
unnamed: R30.2, U12.15 (VOA)
unnamed: R31.2, U12.10 (VOB)
unnamed: R35.1, U12.6 (DT)
unnamed: R40.1, U11.2
unnamed: R53.2, U8.15 (VOA)
unnamed: R54.2, U8.10 (VOB)
unnamed: R57.1, U13.3 (VIOUT)
unnamed: R60.1, U10.3 (VIOUT)
unnamed: R63.2, U14.15 (VOA)
unnamed: R64.2, U14.10 (VOB)
unnamed: R65.1, U14.6 (DT)

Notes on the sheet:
TIM1CH
TIM8CH
Filter:10kohm
Filter:3ohm
2200μF https://jp.rs-online.com/web/p/aluminium-capacitors/7111346/

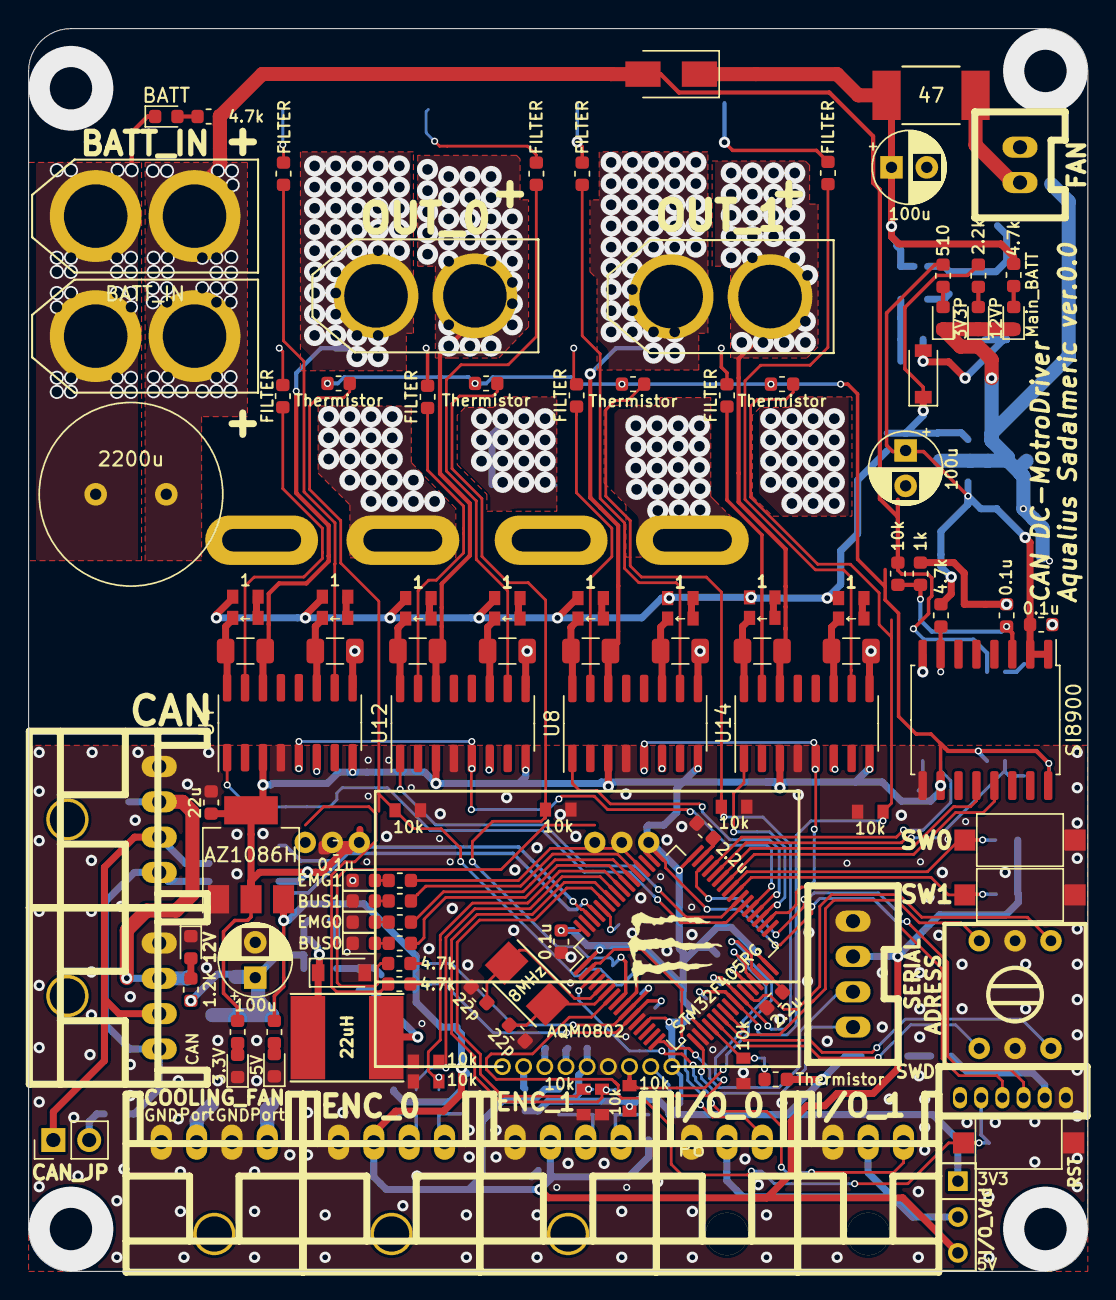
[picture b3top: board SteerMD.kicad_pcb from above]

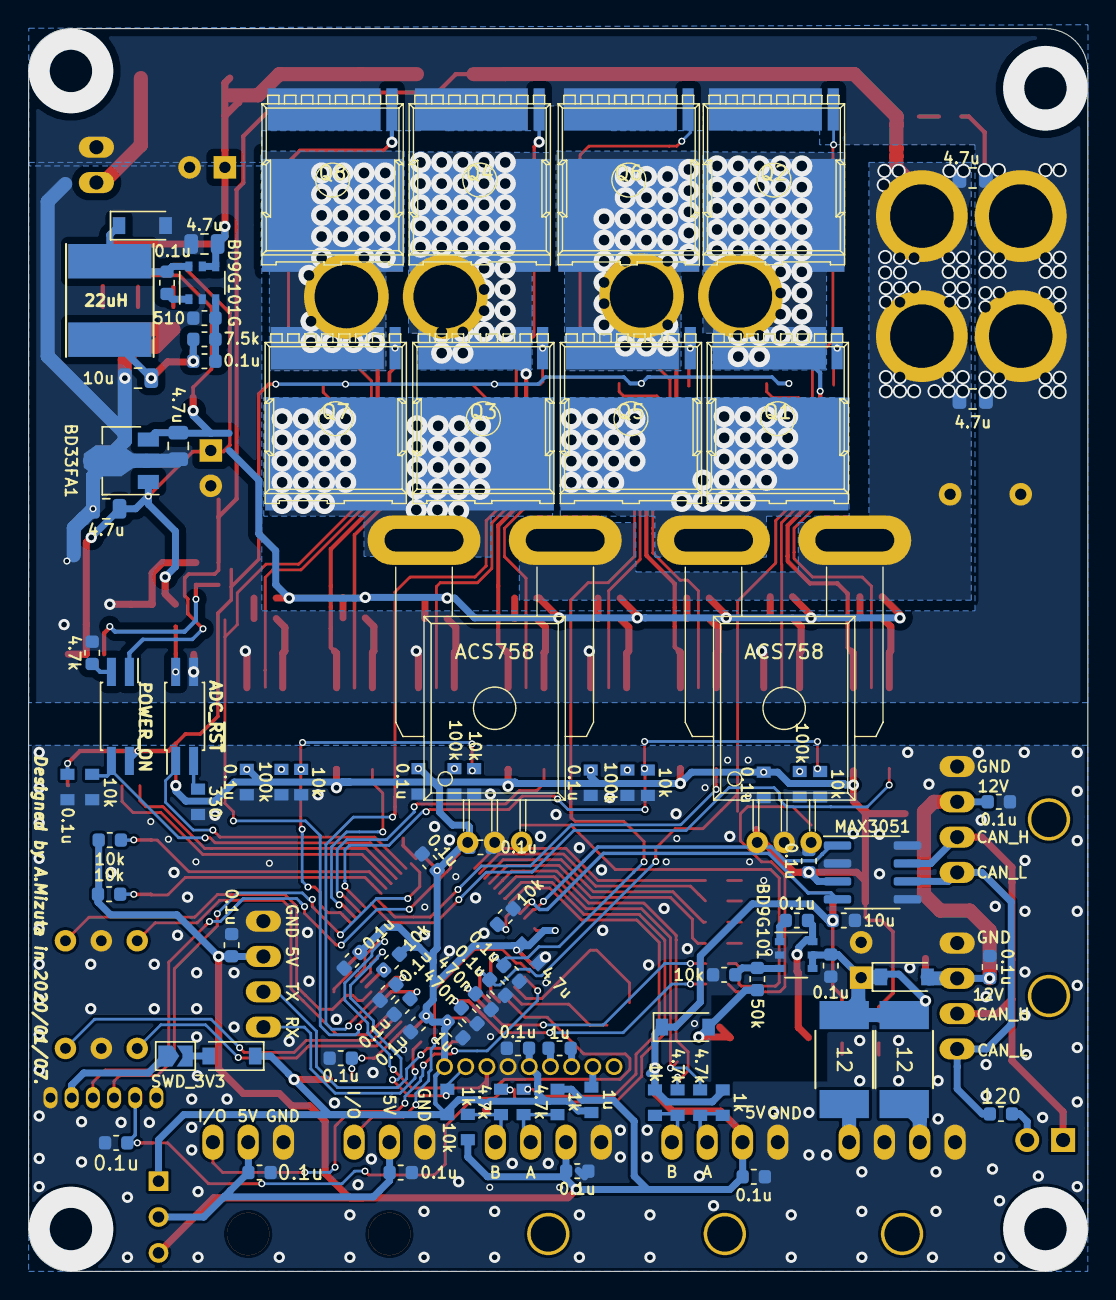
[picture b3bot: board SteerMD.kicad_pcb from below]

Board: 2 copper layers, 75.0 x 88.0 mm, 216 parts (94 on the bottom side), 141 nets.
